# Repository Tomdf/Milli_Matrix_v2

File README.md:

Mini_Matrix_v2
==============

Hardware and software for the Mini-Matrix v2

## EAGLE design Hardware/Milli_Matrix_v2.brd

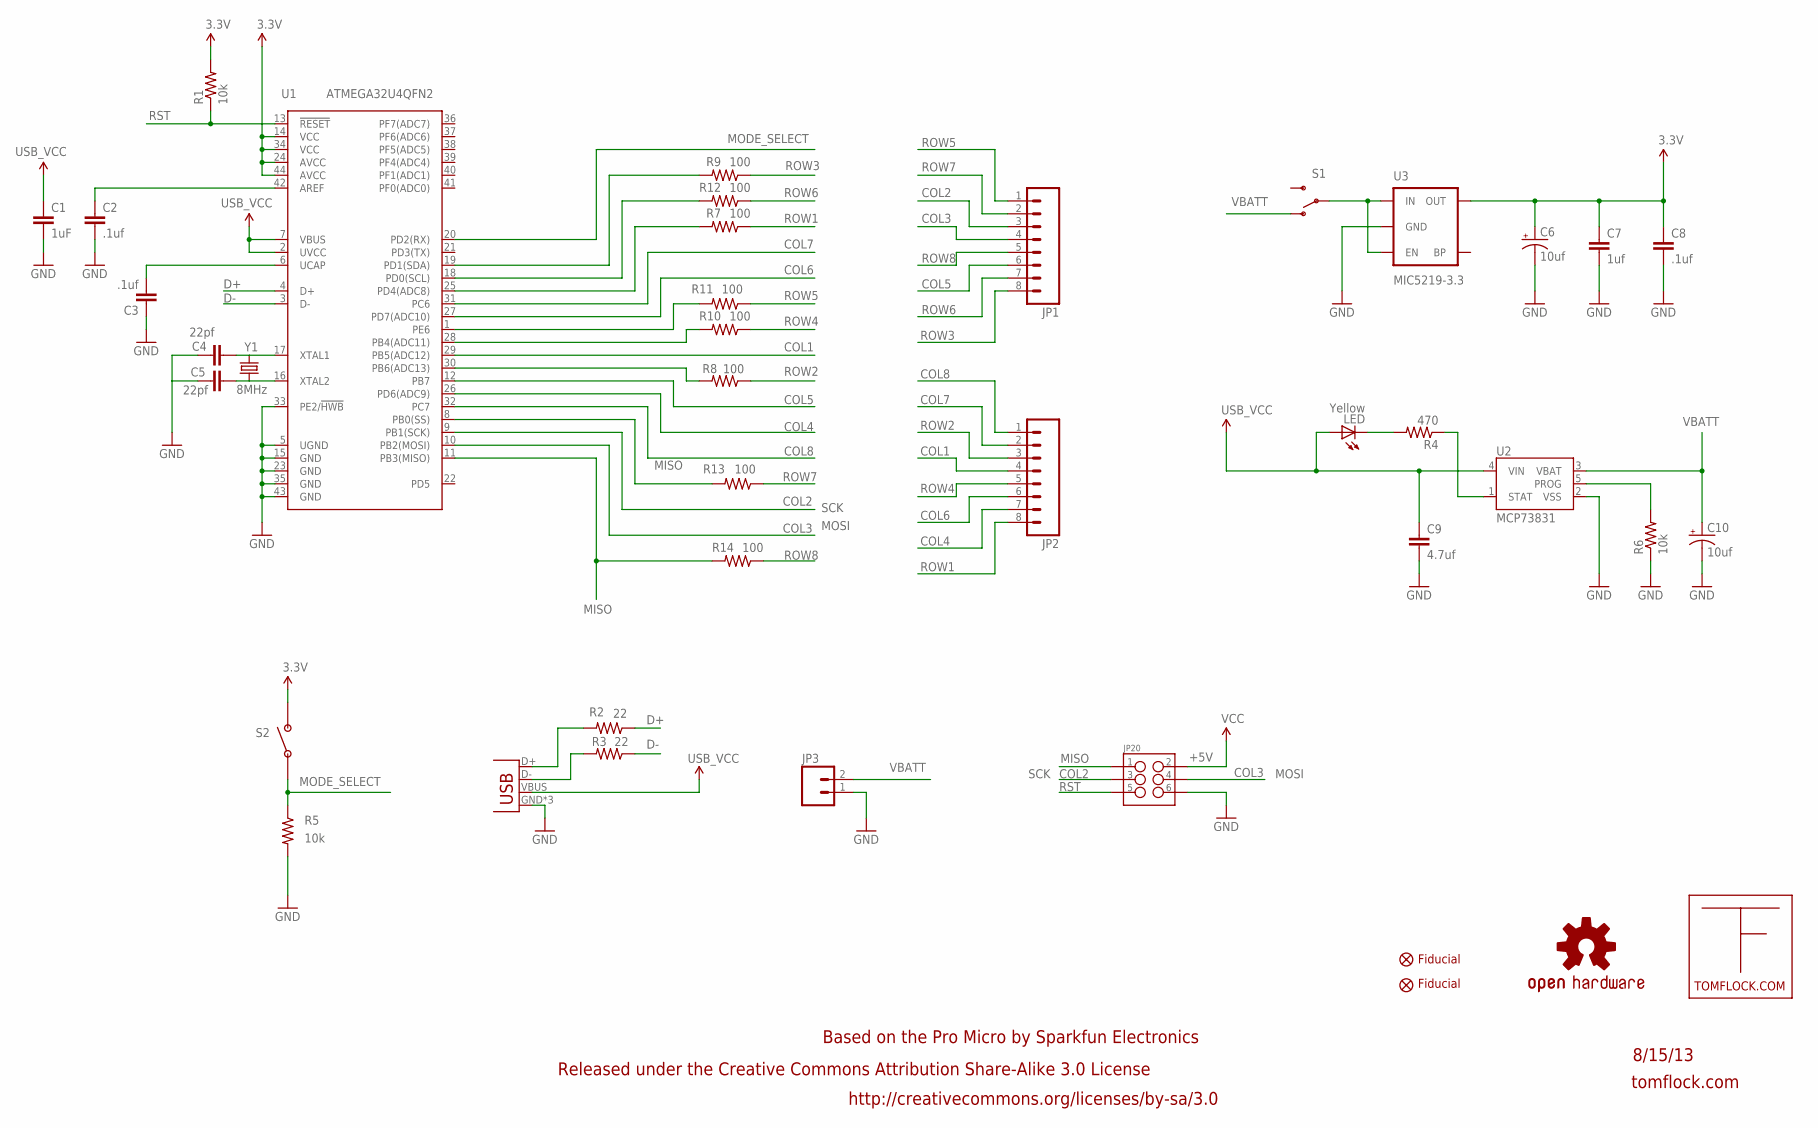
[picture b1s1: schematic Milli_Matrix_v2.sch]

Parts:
C1: 1uF; 0402-CAP
C2, C3, C8: .1uf; 0402-CAP
C4, C5: 22pf; 0402-CAP
C6, C10: 10uf; EIA3216
C7: 1uf; 0402-CAP
C9: 4.7uf; 0402-CAP
JP1, JP2: M08SMD-STRAIGHT; 1X08_SMD
JP3: M02-JST-2-PTH-NO_SILK; JST-2-PTH-NS
JP6, JP7: FIDUCIAL1.5X3; FIDUCIAL-1.5X3
JP20: M03X22X3_SILK_SM; 2X3
LED: Yellow; LED-0603
R1, R5, R6: 10k; 0402-RES
R2, R3: 22; 0402-RES
R4: 470; 0402-RES
R7, R8, R9, R10, R11, R12, R13, R14: 100; 0402-RES
S1: SWITCH-SPST-SMD-A
S2: SWITCH-RIGHT-ANGLE-SMD
U1: ATMEGA32U4QFN2; SPARKFUN-DIGITALIC_QFN-44-NOPAD
U2: MCP73831; SOT23-5
U3: MIC5219-3.3; SOT23-5
U$1: TFLOGO
U$2: OSHW-LOGOS; OSHW-LOGO-S
USB_MICROB: USB-MICROB
Y1: 8MHz; CRYSTAL-SMD-5X3

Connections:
3.3V: C6.A (+), C7.1, C8.1, JP20.2, R1.2, S2.2, U1.14 (VCC), U1.24 (AVCC), U1.34 (VCC), U1.44 (AVCC), U3.5 (OUT)
COL1: JP2.4, U1.29 (PB5(ADC12))
COL2: JP1.3, JP20.3, U1.9 (PB1(SCK))
COL3: JP1.4, JP20.4, U1.10 (PB2(MOSI))
COL4: JP2.7, U1.26 (PD6(ADC9))
COL5: JP1.6, U1.12 (PB7)
COL6: JP2.6, U1.27 (PD7(ADC10))
COL7: JP2.2, U1.31 (PC6)
COL8: JP2.1, U1.32 (PC7)
D+: R2.1, U1.4 (D+)
D-: R3.1, U1.3 (D-)
GND: C1.2, C2.2, C3.1, C4.1, C5.1, C6.C (-), C7.2, C8.2, C9.2, C10.C (-), JP3.1, JP20.6, R5.2, R6.1, U1.5 (UGND), U1.15 (GND), U1.23 (GND), U1.33 (PE2/!HWB), U1.35 (GND), U1.43 (GND), U2.2 (VSS), U3.2 (GND), USB_MICROB.GND, USB_MICROB.MT1 (GND), USB_MICROB.MT2 (GND)
MISO: JP20.1, R14.2, U1.11 (PB3(MISO))
MODE_SELECT: R5.1, S2.1, U1.20 (PD2(RX))
unnamed: S1.2, U3.1 (IN), U3.3 (EN)
unnamed: C5.2, U1.16 (XTAL2), Y1.1
unnamed: R6.2, U2.5 (PROG)
unnamed: C4.2, U1.17 (XTAL1), Y1.3 (2)
unnamed: C2.1, U1.42 (AREF)
unnamed: R4.1, U2.1 (STAT)
unnamed: LED.C, R4.2
unnamed: C3.2, U1.6 (UCAP)
unnamed: R11.2, U1.1 (PE6)
unnamed: R13.2, U1.8 (PB0(SS))
unnamed: R12.2, U1.18 (PD0(SCL))
unnamed: R9.2, U1.19 (PD1(SDA))
unnamed: R3.2, USB_MICROB.D-
unnamed: R2.2, USB_MICROB.D+
unnamed: R8.2, U1.30 (PB6(ADC13))
unnamed: R10.2, U1.28 (PB4(ADC11))
unnamed: R7.2, U1.25 (PD4(ADC8))
ROW1: JP2.8, R7.1
ROW2: JP2.3, R8.1
ROW3: JP1.8, R9.1
ROW4: JP2.5, R10.1
ROW5: JP1.1, R11.1
ROW6: JP1.7, R12.1
ROW7: JP1.2, R13.1
ROW8: JP1.5, R14.1
RST: JP20.5, R1.1, U1.13 (!RESET)
VBATT: C10.A (+), JP3.2, S1.1 (O), U2.3 (VBAT)
VCC: C1.1, C9.1, LED.A, U1.2 (UVCC), U1.7 (VBUS), U2.4 (VIN), USB_MICROB.VBUS

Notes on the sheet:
SCK
MOSI
+5V
Released under the Creative Commons Attribution Share-Alike 3.0 License
http://creativecommons.org/licenses/by-sa/3.0
tomflock.com
8/15/13
Based on the Pro Micro by Sparkfun Electronics
Fiducial

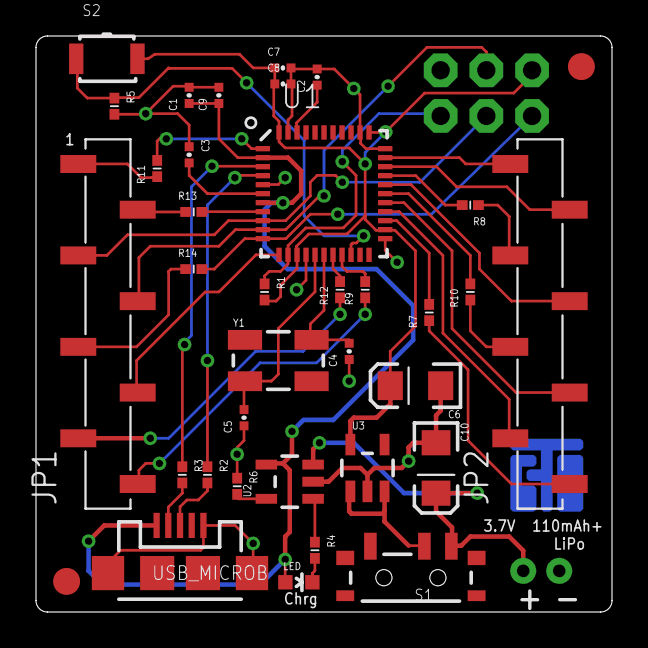
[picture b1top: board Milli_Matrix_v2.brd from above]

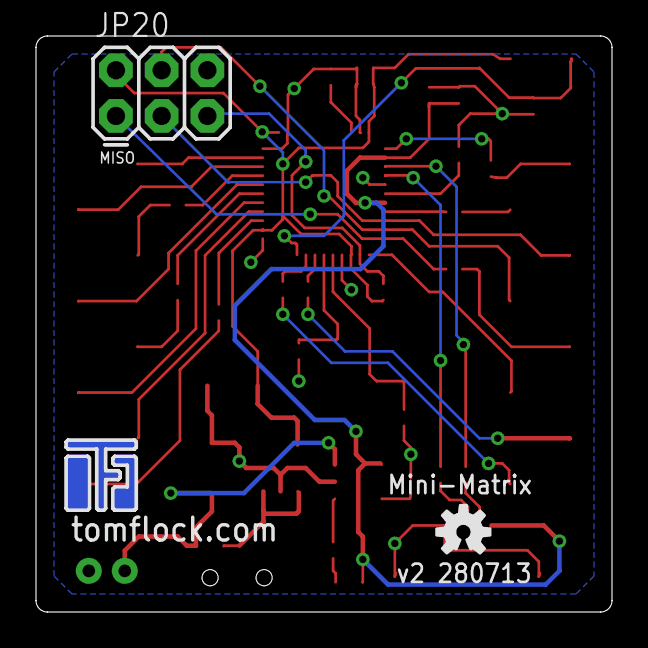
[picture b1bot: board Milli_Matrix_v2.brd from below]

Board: 2 copper layers, 32.0 x 32.0 mm, 40 parts (3 on the bottom side), 42 nets.

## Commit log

2013-08-12 Initial Commit
    EaglePCB schematic and board files
2013-08-16 Added detailed Documentation
    Assembly Drawing
    Schematic
    Stencil
2013-08-16 Schematic Cleanup
    Tweaked the schematic layout for aesthetics and reason.
2013-08-17 LED DataSheet and Bootloader Instructions
2013-08-19 Rename and Arduino Code
    Got matrix work good, tired
    sleep good
    ss==
2013-08-20 Updates to Arduino Code
    Set up a definitions file for the MRSKULL pattern arrays.
    Added a second mode, although I forget the name.. Biting Skull?
    Whatever, it is two frames, one with the mouth open and the other with
    mouth closed.
    Played around with the brightness by removing the delay for blank pixels
    (so that ON pixels were ON more ONften. Then set the leds to stay lit
2013-08-22 PCB Cleanup + back solder pads for mounting
    Tweaked some of the component placements
    Put some rectangles on the back of the board in hopes of soldering
    safety pins to them.
2013-08-26 Adjusted definitions.h
    Renamed the definitions.h file from MRSKULL to millMATRIX.
    Cleaned up the "firmware" burning instructions.
2013-08-27 Even more definitions!
    Moar definitions for you!
2013-08-27 New Animations Sketch
    Started a new sketch for different sets of two frame animations. Biting
    skull, and two invaders
2013-08-28 Renamed some files, worked on animations
2013-08-30 More Definition Work
2013-08-31 More foolin around with libraries
    didn't get anything accomplished other than learning that C doesn't have
    arrays, it has pointers.
2013-09-05 All around organization and cleanup for presentation
2013-09-11 Update to stencil
2014-01-25 Added the heart animation

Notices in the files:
parts and their libraries:
SparkFun: Licensing: CC v3.0 Share-Alike You are welcome to use this library for commercial purposes.
